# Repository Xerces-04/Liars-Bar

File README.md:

# Liar's Bar: Tabletop Hardware Edition

An interactive, embedded implementation of the *Liar's Bar* revolver / Russian Roulette game mechanic built on Arduino. The project features randomized chamber states, dynamic LED indicator animations, synchronized audio cues via a DFPlayer Mini, real-time life tracking on a 7-segment display, and a dedicated 3D-printable square enclosure with heat-set threaded inserts.

---

## Features

* **True-Random Cylinder Spin:** Seeds pseudo-random generation using floating analog noise on pin `A0` combined with a Fisher-Yates array shuffle.
* **Synchronized Audio System:** Multi-channel sound effects driven by the DFPlayer Mini:
  * Cylinder spinning & cocking on startup/reload
  * Hammer cock on trigger pull
  * Dry fire click on safe rounds
  * Gunshot on live rounds
* **Visual Status Indicators:**
  * **TM1637 4-Digit Display:** Tracks remaining chamber counts (`6` down to `1`) and displays a custom `dEAd` segment pattern on elimination.
  * **6-LED Array:** 5 Green LEDs (safe chambers) and 1 Red LED (lethal chamber) with dynamic spinning deceleration sequences.
* **Rugged Enclosure Design:** Two-part square enclosure (base + lid) joined via four M3 heat-set brass inserts, featuring front-facing power and status readouts and top-mounted player controls.

---

## System Architecture & Pinout

```
                           +-------------------+
                           |    Arduino Uno/   |
                           |    Nano (MCU)     |
                           +---------+---------+
                                     |
      +---------------+--------------+--------------+---------------+
      |               |              |              |               |
+-----+-----+   +-----+-----+  +-----+-----+  +-----+-----+   +-----+-----+
|  TM1637   |   | DFPlayer  |  | 6x LED    |  | Fire      |   | Power     |
| 7-Segment |   |   Mini    |  | Array     |  | Pushbutton|   | Rocker    |
| (CLK/DIO) |   | (Software |  | (5G / 1R) |  | (Pullup)  |   | Switch    |
|           |   |  Serial)  |  |           |  |           |   |           |
+-----------+   +-----------+  +-----------+  +-----------+   +-----------+
```

### Pin Assignment Table

| Arduino Pin | Connected Hardware | Signal / Mode | Description |
| :--- | :--- | :--- | :--- |
| **D2** | Green LED 1 (`G1`) | `OUTPUT` | Safe Chamber 1 Indicator |
| **D3** | Green LED 2 (`G2`) | `OUTPUT` | Safe Chamber 2 Indicator |
| **D4** | Green LED 3 (`G3`) | `OUTPUT` | Safe Chamber 3 Indicator |
| **D5** | Green LED 4 (`G4`) | `OUTPUT` | Safe Chamber 4 Indicator |
| **D6** | Green LED 5 (`G5`) | `OUTPUT` | Safe Chamber 5 Indicator |
| **D7** | Red LED 1 (`R1`) | `OUTPUT` | Lethal Chamber Indicator |
| **D8** | TM1637 Display | `OUTPUT` | Display Clock (`CLK`) |
| **D9** | Push Button | `INPUT_PULLUP`| Fire / Trigger / Reset Action |
| **D10** | TM1637 Display | `OUTPUT` | Display Data I/O (`DIO`) |
| **D11** | DFPlayer Mini `RX` | `OUTPUT` (SoftSerial) | Arduino TX → DFPlayer RX (via 1kΩ resistor) |
| **D12** | DFPlayer Mini `TX` | `INPUT` (SoftSerial) | Arduino RX ← DFPlayer TX |
| **A0** | *Unconnected* | `INPUT` | Floating ADC input for random entropy |
| **A1** | DFPlayer Mini `BUSY`| `INPUT` | Audio playback status monitoring |

---

## Custom PCB Design

A custom carrier PCB was designed in KiCad/EasyEDA to eliminate messy point-to-point breadboard wiring, consolidate the pullups and current-limiting resistors, and fit snugly inside the 3D-printed enclosure.

| Schematic View | 3D Board Render |
| :---: | :---: |
|  |  |

### PCB Highlights & Specifications
* **Form Factor:** Custom dual-layer FR-4 board (2-layer, 1.6mm thickness).
* **Socketed Modules:** Direct female header sockets for the **Arduino Nano** and **DFPlayer Mini** to allow easy swapping and reprogramming.
* **Onboard Power Conditioning:** 
  * Integrated bypass capacitors across `VCC`/`GND` rails to prevent audio buzz/pops from the DFPlayer Mini amplifier.
  * Dedicated JST-XH / screw-terminal power input header connected in series with the rocker switch line.
* **Direct Panel Breakouts:** JST-XH connector pads for off-board panel-mounted components (TM1637 Display, Trigger Button, Speaker, and Power Switch).
* **LED Array Layout:** Arranged radially on-board (or via ribbon header to the top lid) with integrated SMD/THT current-limiting resistors.

> Gerber and drill files for PCB manufacturing are available in the [`Gerbers`](Gerbers) directory.

---

## Bill of Materials (BOM)

### Electronics
* 1x Custom Carrier PCB (or standard prototyping perfboard)
* 1x Arduino Nano, Uno, or Pro Micro (ATmega328P based)
* 1x DFPlayer Mini MP3 Module
* 1x MicroSD Card (FAT32 formatted, 32GB max)
* 1x 8Ω 0.5W–3W Dynamic Speaker
* 1x TM1637 4-Digit 7-Segment Display Module
* 5x 5mm Green LEDs
* 1x 5mm Red LED
* 6x 220Ω–330Ω Current-Limiting Resistors (for LEDs)
* 1x 1kΩ Resistor (serial line noise suppression between Arduino D11 & DFPlayer RX)
* 1x SPST Rocker Switch (panel-mount)
* 1x SPST Momentary Push Button (panel-mount, top trigger)
* 1x 9V Battery clip or 5V USB breakout board for power

### Hardware & Enclosure
* 4x M3 Brass Heat-Set Threaded Inserts (e.g., M3 x 4mm or M3 x 5.7mm OD)
* 4x M3 Button Head / Socket Head Machine Screws (M3 x 8mm–12mm)
* 1x 3D-Printed Custom Base Enclosure
* 1x 3D-Printed Custom Top Lid

---

## Enclosure Layout & Mechanical Details

* **Front Panel:**
  * Rectangular cutout for the 4-digit TM1637 7-segment display.
  * Rectangular/round cutout for the main SPST rocker power switch.
* **Top Panel (Lid):**
  * Central mounting hole for the trigger push button.
  * 6x Circular bezel holes arranged in an arc/circle for the 5 green LEDs and 1 red LED.
* **Base Mounting:**
  * Four internal corner bosses with pilot holes sized for M3 heat-set inserts.
  * The top lid secures to the base using four countersunk M3 machine screws.

---

## MicroSD Card Setup

1. Format your MicroSD card to **FAT32**.
2. Create a root folder named `01`.
3. Add the following audio files formatted as standard MP3s:

```text
SD_CARD_ROOT/
└── 01/
    ├── 001.mp3  # Spare / reserved
    ├── 002.mp3  # Hammer cock / trigger pull
    ├── 003.mp3  # Dry fire / safe chamber click
    ├── 004.mp3  # Cylinder spin & reload sound
    └── 005.mp3  # Gunshot / lethal round
```

---

## Software Installation & Dependencies

### 1. Required Libraries
Install the following libraries via the Arduino IDE Library Manager (**Sketch → Include Library → Manage Libraries**):
* **`TM1637Display`** by Avishay Orpaz
* **`DFRobotDFPlayerMini`** by DFRobot
* **`SoftwareSerial`** (Included standard with the Arduino AVR core)

### 2. Flashing the Firmware
1. Clone this repository:
   ```bash
   git clone https://github.com/your-username/liars-bar-arduino.git
   ```
2. Open `liars_bar_arduino.ino` in the Arduino IDE.
3. Under **Tools → Board**, select your target board (e.g., **Arduino Nano**).
4. Select the correct **Processor** (e.g., ATmega328P or ATmega328P Old Bootloader) and **Port**.
5. Compile and upload the sketch.

---

## State Machine & Game Logic Flow

```
   [ POWER ON ]
        │
        ▼
   [ State 7: Spin / Init ] ──> Play Sound 004 & Decelerating LED Spin
        │
        ▼ (Press Fire Button)
  ┌─────┴────────────────────────────────────────────────┐
  │ Check randomPins[current_round]                      │
  ├──────────────────────────────┬───────────────────────┤
  │ If Safe Pin (Pins 2-6)       │ If Lethal Pin (Pin 7) │
  ▼                              ▼                       ▼
[ Dry Fire ]                   [ Wet Fire ]
- Decrement lives (6 -> 1)     - Play Sound 002 -> 005
- Play Sound 002 -> 003        - Flash Pin 7 (Red LED)
- Flash corresponding Pin      - Display "dEAd"
- Advance State (8 -> 12)      - Move to State 13 (Game Over)
  │                              │
  └──────────────┬───────────────┘
                 │
                 ▼
         [ State 13: Game Over ]
                 │
                 ▼ (Press Fire Button)
         [ Reset Game ]
         - Re-seed & Fisher-Yates array shuffle
         - Reset display to 6 lives
         - Trigger reload sound & spin sequence
         - Return to State 7
```

---

## Finished Build Gallery

| Assembled Unit | Internal Hardware & PCB Fit |
| :---: | :---: |
|  |  |

---

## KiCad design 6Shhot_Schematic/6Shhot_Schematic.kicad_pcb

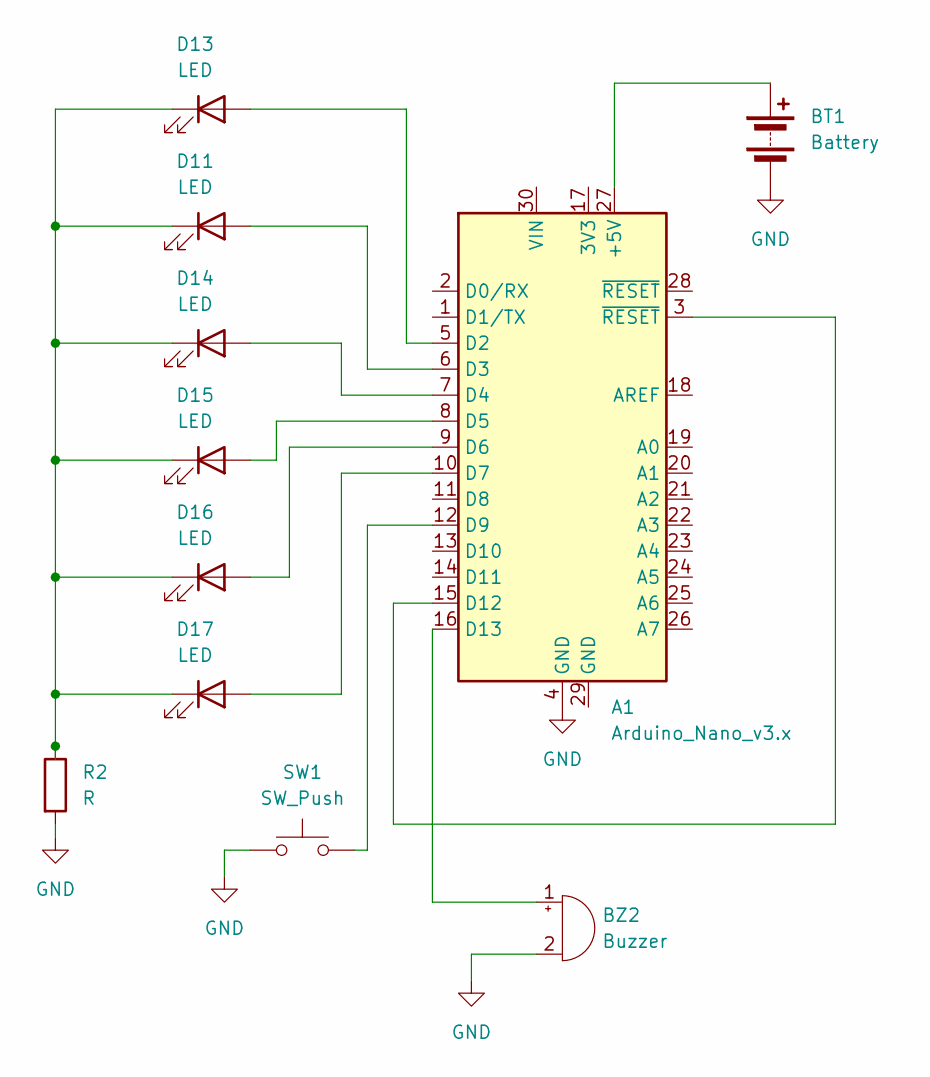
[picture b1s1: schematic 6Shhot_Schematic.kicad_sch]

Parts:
A1: Arduino_Nano_v3.x; Arduino_Nano
BT1: Battery; R_0201_0603Metric
BZ2: Buzzer; Buzzer_12x9.5RM7.6
D11, D13, D14, D15, D16, D17: LED; LED_D5.0mm
R2: R; R_Axial_DIN0516_L15.5mm_D5.0mm_P5.08mm_Vertical
SW1: SW_Push; SW_SPST_EVPBF

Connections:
GND: A1.4 (GND), BT1.2 (-), BZ2.2 (-), R2.2, SW1.1
unnamed: A1.27 (+5V), BT1.1 (+)
unnamed: A1.5 (D2), D13.2 (A)
unnamed: A1.6 (D3), D11.2 (A)
unnamed: A1.7 (D4), D14.2 (A)
unnamed: A1.8 (D5), D15.2 (A)
unnamed: A1.9 (D6), D16.2 (A)
unnamed: A1.10 (D7), D17.2 (A)
unnamed: A1.12 (D9), SW1.2
unnamed: A1.3 (~RESET), A1.15 (D12)
unnamed: A1.16 (D13), BZ2.1 (+)
unnamed: D11.1 (K), D13.1 (K), D14.1 (K), D15.1 (K), D16.1 (K), D17.1 (K), R2.1

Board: 2 copper layers, 11 parts (0 on the bottom side), 12 nets, no tracks yet.
